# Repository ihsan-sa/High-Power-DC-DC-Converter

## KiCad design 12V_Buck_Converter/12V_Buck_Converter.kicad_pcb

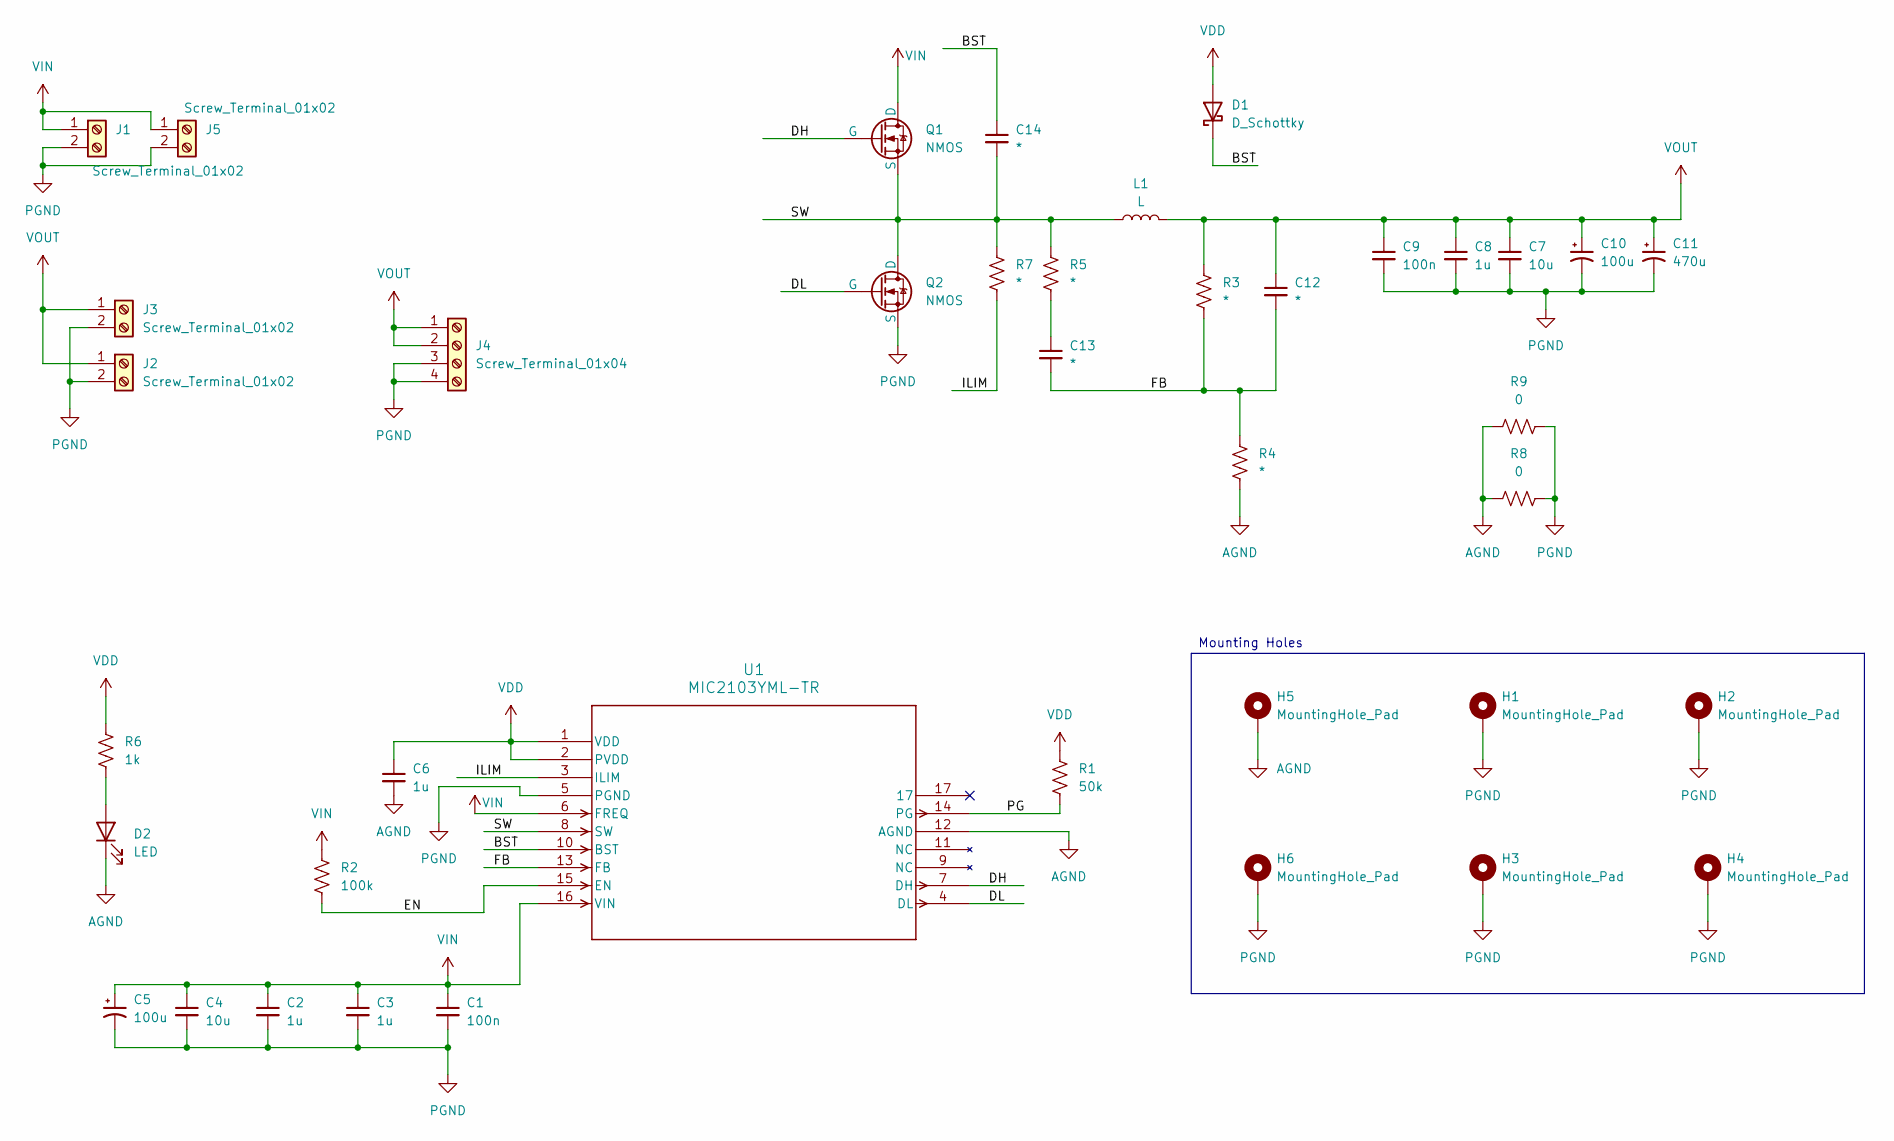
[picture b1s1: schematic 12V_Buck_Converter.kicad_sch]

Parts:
C1, C9: 100n; C_0603_1608Metric_Pad1.08x0.95mm_HandSolder
C2, C3, C6, C8: 1u; C_0603_1608Metric_Pad1.08x0.95mm_HandSolder
C4, C7: 10u; C_0603_1608Metric_Pad1.08x0.95mm_HandSolder
C5, C10: 100u; CP_Radial_D8.0mm_P3.80mm
C11: 470u; CP_Radial_D10.0mm_P5.00mm
C12, C13, C14: *; C_0603_1608Metric_Pad1.08x0.95mm_HandSolder
D1: D_Schottky; D_SOD-323F
D2: LED; LED_0603_1608Metric_Pad1.05x0.95mm_HandSolder
H1, H2, H3, H4, H5, H6: MountingHole_Pad; MountingHole_3.2mm_M3_Pad
J1, J2, J3: Screw_Terminal_01x02; TerminalBlock_MetzConnect_Type701_RT11L02HGLU_1x02_P6.35mm_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
J4: Screw_Terminal_01x04; TerminalBlock_MaiXu_MX126-5.0-04P_1x04_P5.00mm
J5: Screw_Terminal_01x02; TerminalBlock_MetzConnect_Type094_RT03502HBLU_1x02_P5.00mm_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
L1: L; inductor
Q1, Q2: NMOS; TRANS_IAUZ20N08S5L300ATMA1
R1: 50k; R_0603_1608Metric_Pad0.98x0.95mm_HandSolder
R2: 100k; R_0603_1608Metric_Pad0.98x0.95mm_HandSolder
R3, R4, R5, R7: *; R_0603_1608Metric_Pad0.98x0.95mm_HandSolder
R6: 1k; R_0603_1608Metric_Pad0.98x0.95mm_HandSolder
R8, R9: 0; R_1206_3216Metric_Pad1.30x1.75mm_HandSolder
U1: MIC2103YML-TR; MLF-16_ML_4X4_MCH

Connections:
/BST: C14.1, D1.1 (K), U1.10 (BST)
/DH: Q1.2 (G), U1.7 (DH)
/DL: Q2.2 (G), U1.4 (DL)
/EN: R2.2, U1.15 (EN)
/FB: C12.2, C13.2, R3.2, R4.1, U1.13 (FB)
/ILIM: R7.2, U1.3 (ILIM)
/PG: R1.2, U1.14 (PG)
/SW: C14.2, L1.1, Q1.3 (S), Q2.1 (D), R5.1, R7.1, U1.8 (SW)
AGND: C6.2, D2.1 (K), H5.1, R4.2, R8.1, R9.1, U1.12 (AGND)
unnamed: C13.1, R5.2
unnamed: D2.2 (A), R6.2
PGND: C1.2, C2.2, C3.2, C4.2, C5.2, C7.2, C8.2, C9.2, C10.2, C11.2, H1.1, H2.1, H3.1, H4.1, H6.1, J1.2, J2.2, J3.2, J4.3, J4.4, J5.2, Q2.3 (S), R8.2, R9.2, U1.5 (PGND)
VDD: C6.1, D1.2 (A), R1.1, R6.1, U1.1 (VDD), U1.2 (PVDD)
VIN: C1.1, C2.1, C3.1, C4.1, C5.1, J1.1, J5.1, Q1.1 (D), R2.1, U1.6 (FREQ), U1.16 (VIN)
VOUT: C7.1, C8.1, C9.1, C10.1, C11.1, C12.1, J2.1, J3.1, J4.1, J4.2, L1.2, R3.1

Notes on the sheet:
Mounting Holes

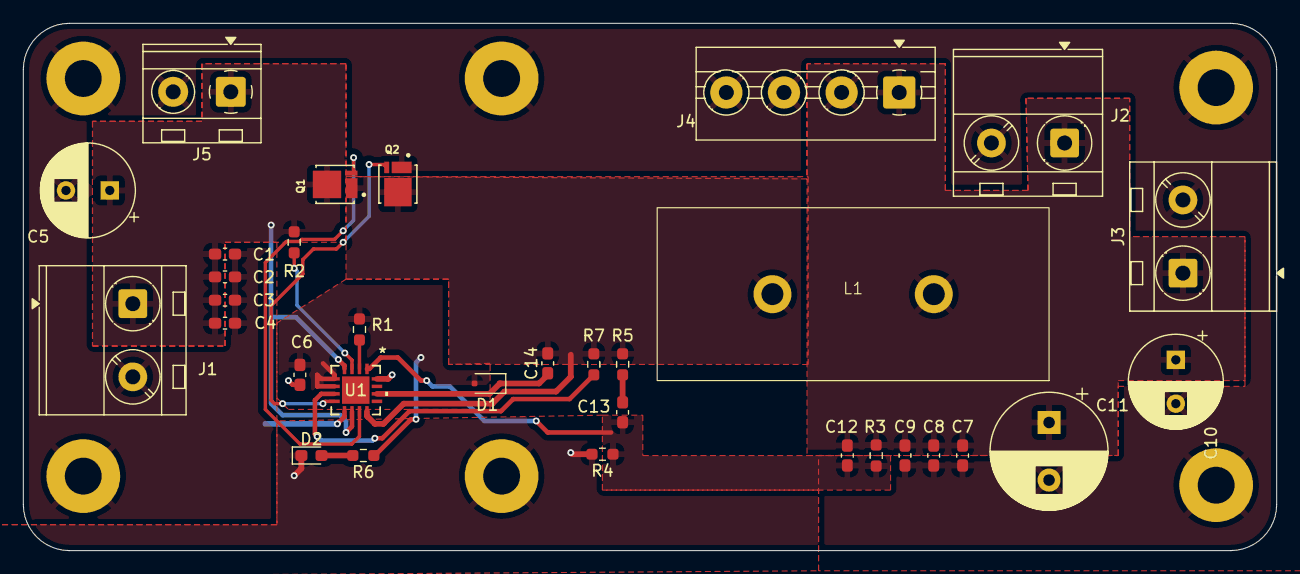
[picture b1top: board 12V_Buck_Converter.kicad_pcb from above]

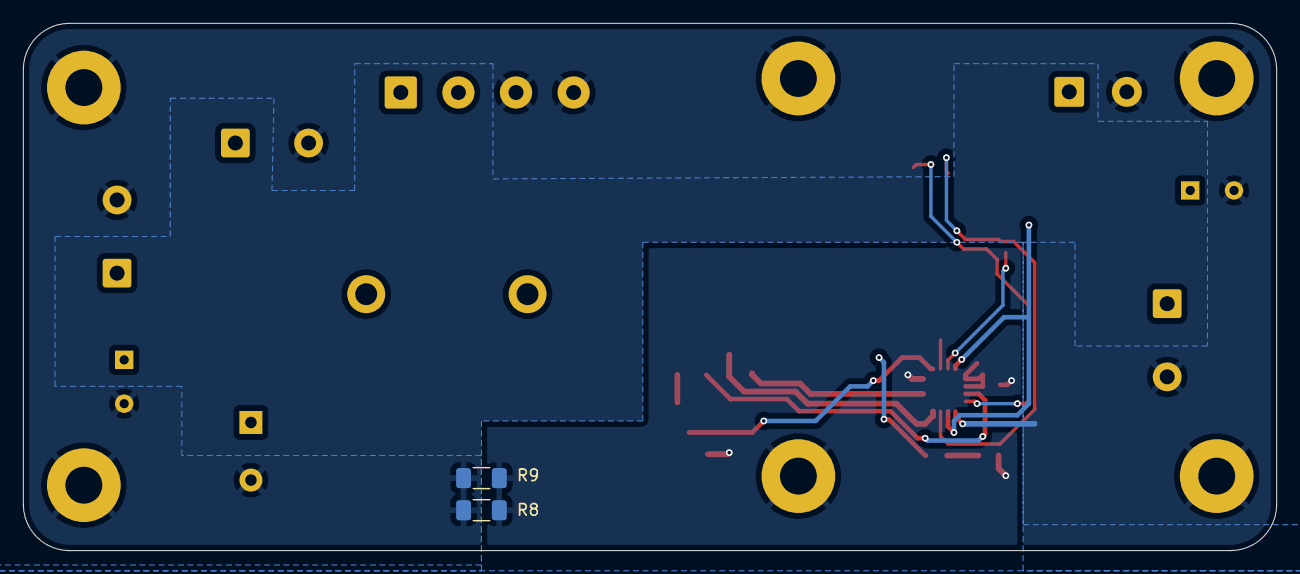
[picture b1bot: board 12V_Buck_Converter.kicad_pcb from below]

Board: 2 copper layers, 108.8 x 45.8 mm, 40 parts (3 on the bottom side), 15 nets.

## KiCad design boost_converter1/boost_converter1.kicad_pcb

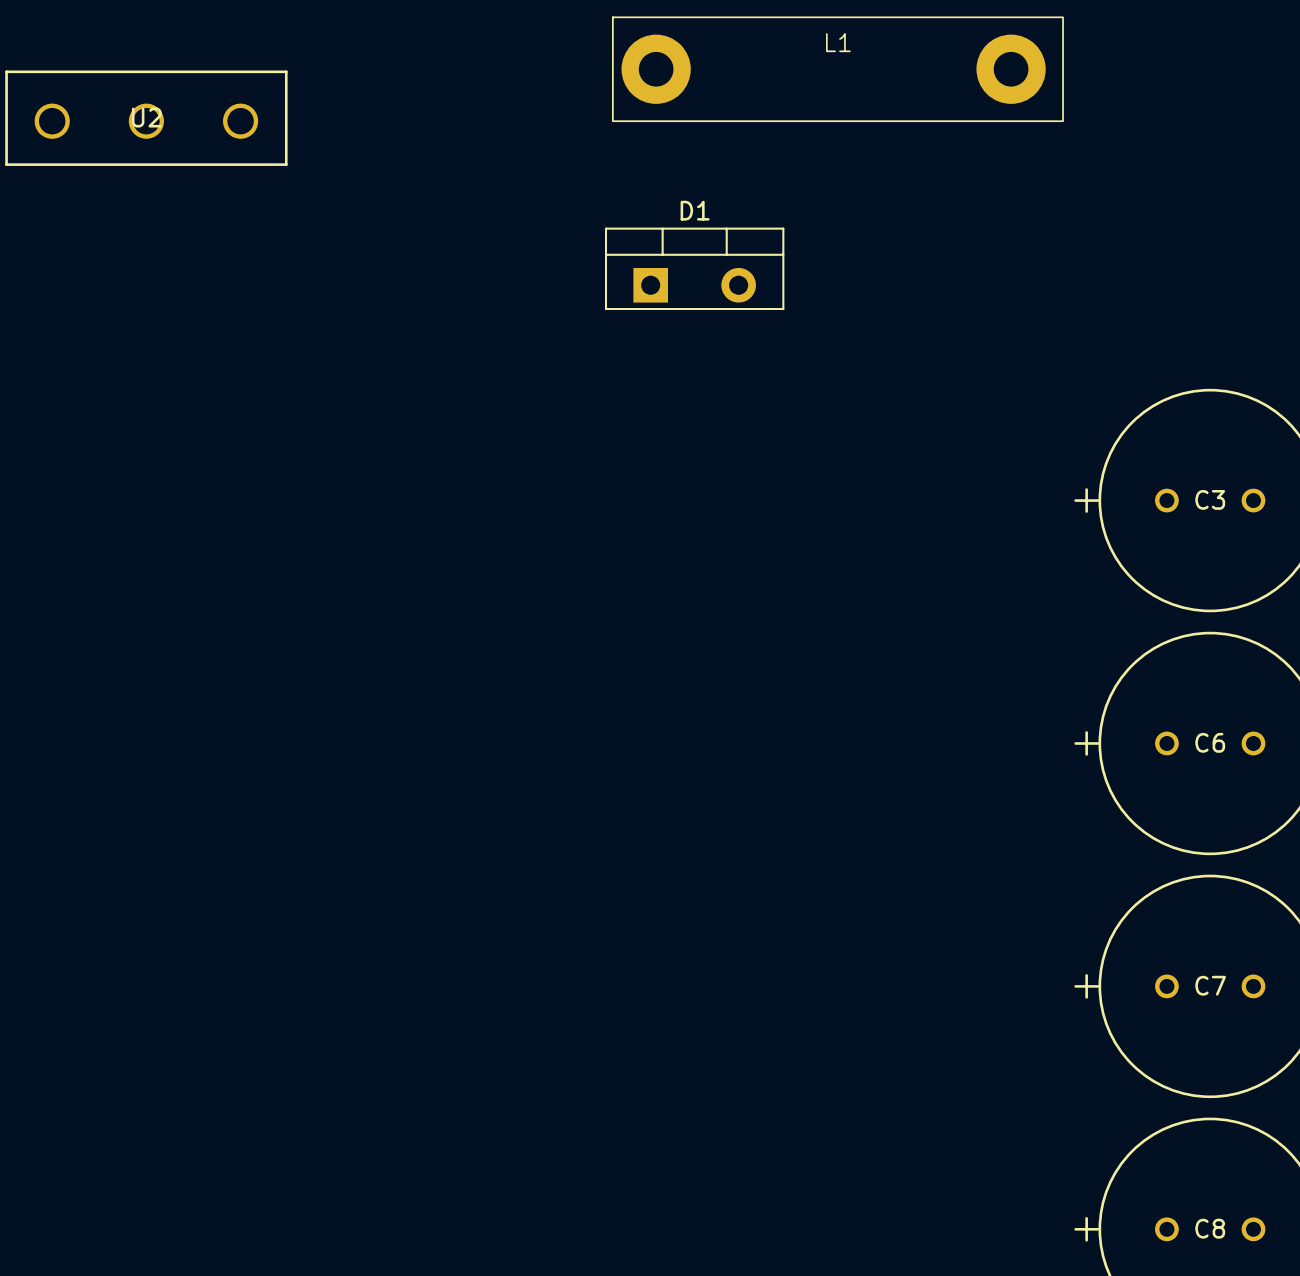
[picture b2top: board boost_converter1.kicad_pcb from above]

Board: 2 copper layers, 7 parts (0 on the bottom side), 3 nets, no tracks yet.

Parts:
C3, C6, C7, C8: UVZ2A331MHD1TO; CAP_UEP_12P5X25_NCH
D1: SDUR30Q65; TO-220-2_Vertical
L1: L; 200uHCustomL
U2: IRFP260NPBF; PG-TO247-3-46_INF

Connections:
/Power_Stage/BOOST_FET_DRAIN: D1.2 (A), L1.2, U2.2 (D)
/Power_Stage/BOOST_OUTPUT: C3.1, C6.1, C7.1, C8.1, D1.1 (K)
GND: C3.2, C6.2, C7.2, C8.2, U2.3 (S)

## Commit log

2025-04-06 Updated components and footprints for power stage.
2025-04-10 [HW] Added MCU supporting components and programming connector.
2025-04-10 [FW] Created STM32 project and completed preliminary pinout setup.
2025-04-10 [HW] Updated components and footprints for power stage.
2025-04-21 [FW] [NUCLEO] Started fleshing out FW.
    - Added input handler.
    - Added PWM generation.
2025-04-21 [FW] Started fleshing out some basic functionality.
2025-04-21 [HW] Auto generated files.
2025-09-14 {12V_Buck_Converter}[HW] Design progress.
2025-09-14 {USB_C_Converter_Board}[HW] Added project here.
2025-09-14 {buck_boost}[HW] Design progress
2025-09-14 Maintenance
